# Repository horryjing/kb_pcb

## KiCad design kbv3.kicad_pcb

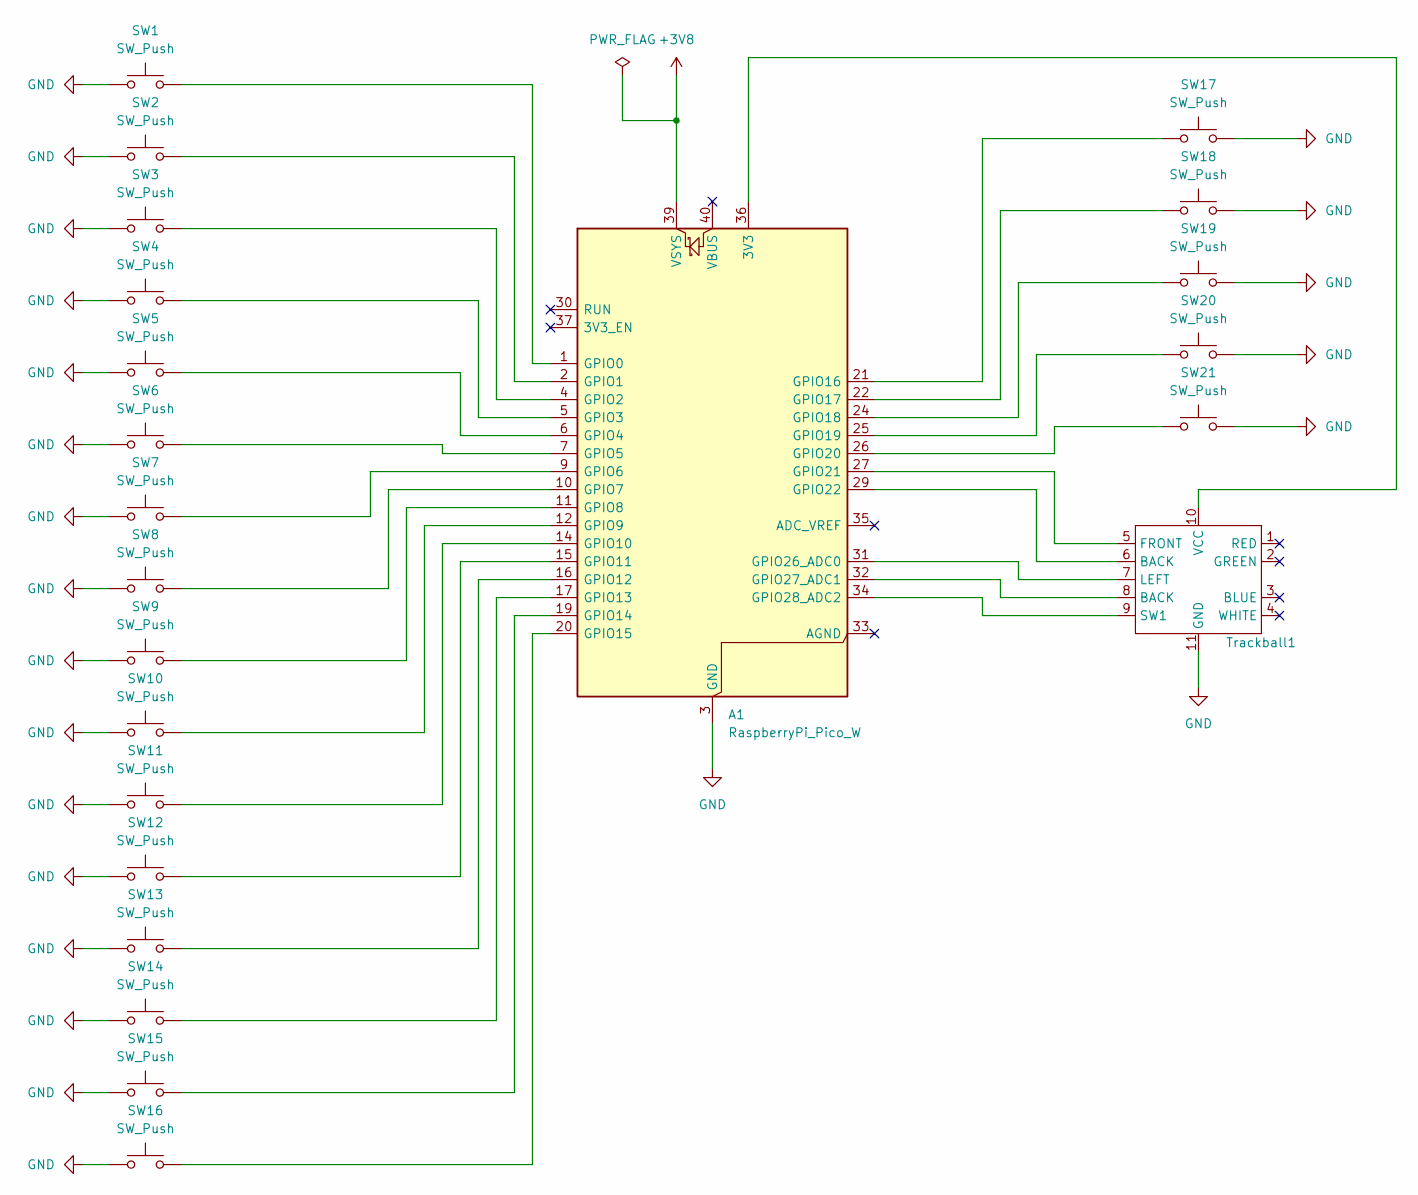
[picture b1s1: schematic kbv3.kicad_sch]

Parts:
A1: RaspberryPi_Pico_W; RaspberryPi_Pico_Common_THT
SW1, SW2, SW3, SW4, SW5, SW6, SW7, SW8, SW9, SW10, SW11, SW12, SW13, SW14, SW15, SW16, SW17, SW18, SW19, SW20, SW21: SW_Push; Kailh_socket_MX
Trackball1: Trackball_footprint

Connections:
+3V8: A1.39 (VSYS)
GND: A1.3 (GND), A1.8 (GND), A1.13 (GND), A1.18 (GND), A1.23 (GND), A1.28 (GND), A1.38 (GND), SW1.1, SW2.1, SW3.1, SW4.1, SW5.1, SW6.1, SW7.1, SW8.1, SW9.1, SW10.1, SW11.1, SW12.1, SW13.1, SW14.1, SW15.1, SW16.1, SW17.2, SW18.2, SW19.2, SW20.2, SW21.2, Trackball1.11 (GND)
unnamed: A1.1 (GPIO0), SW1.2
unnamed: A1.2 (GPIO1), SW2.2
unnamed: A1.4 (GPIO2), SW3.2
unnamed: A1.5 (GPIO3), SW4.2
unnamed: A1.6 (GPIO4), SW5.2
unnamed: A1.7 (GPIO5), SW6.2
unnamed: A1.9 (GPIO6), SW7.2
unnamed: A1.10 (GPIO7), SW8.2
unnamed: A1.11 (GPIO8), SW9.2
unnamed: A1.12 (GPIO9), SW10.2
unnamed: A1.14 (GPIO10), SW11.2
unnamed: A1.15 (GPIO11), SW12.2
unnamed: A1.16 (GPIO12), SW13.2
unnamed: A1.17 (GPIO13), SW14.2
unnamed: A1.19 (GPIO14), SW15.2
unnamed: A1.20 (GPIO15), SW16.2
unnamed: A1.21 (GPIO16), SW17.1
unnamed: A1.22 (GPIO17), SW18.1
unnamed: A1.24 (GPIO18), SW19.1
unnamed: A1.25 (GPIO19), SW20.1
unnamed: A1.26 (GPIO20), SW21.1
unnamed: A1.27 (GPIO21), Trackball1.5 (FRONT)
unnamed: A1.29 (GPIO22), Trackball1.6 (BACK)
unnamed: A1.31 (GPIO26_ADC0), Trackball1.7 (LEFT)
unnamed: A1.32 (GPIO27_ADC1), Trackball1.8 (BACK)
unnamed: A1.34 (GPIO28_ADC2), Trackball1.9 (SW1)
unnamed: A1.36 (3V3), Trackball1.10 (VCC)

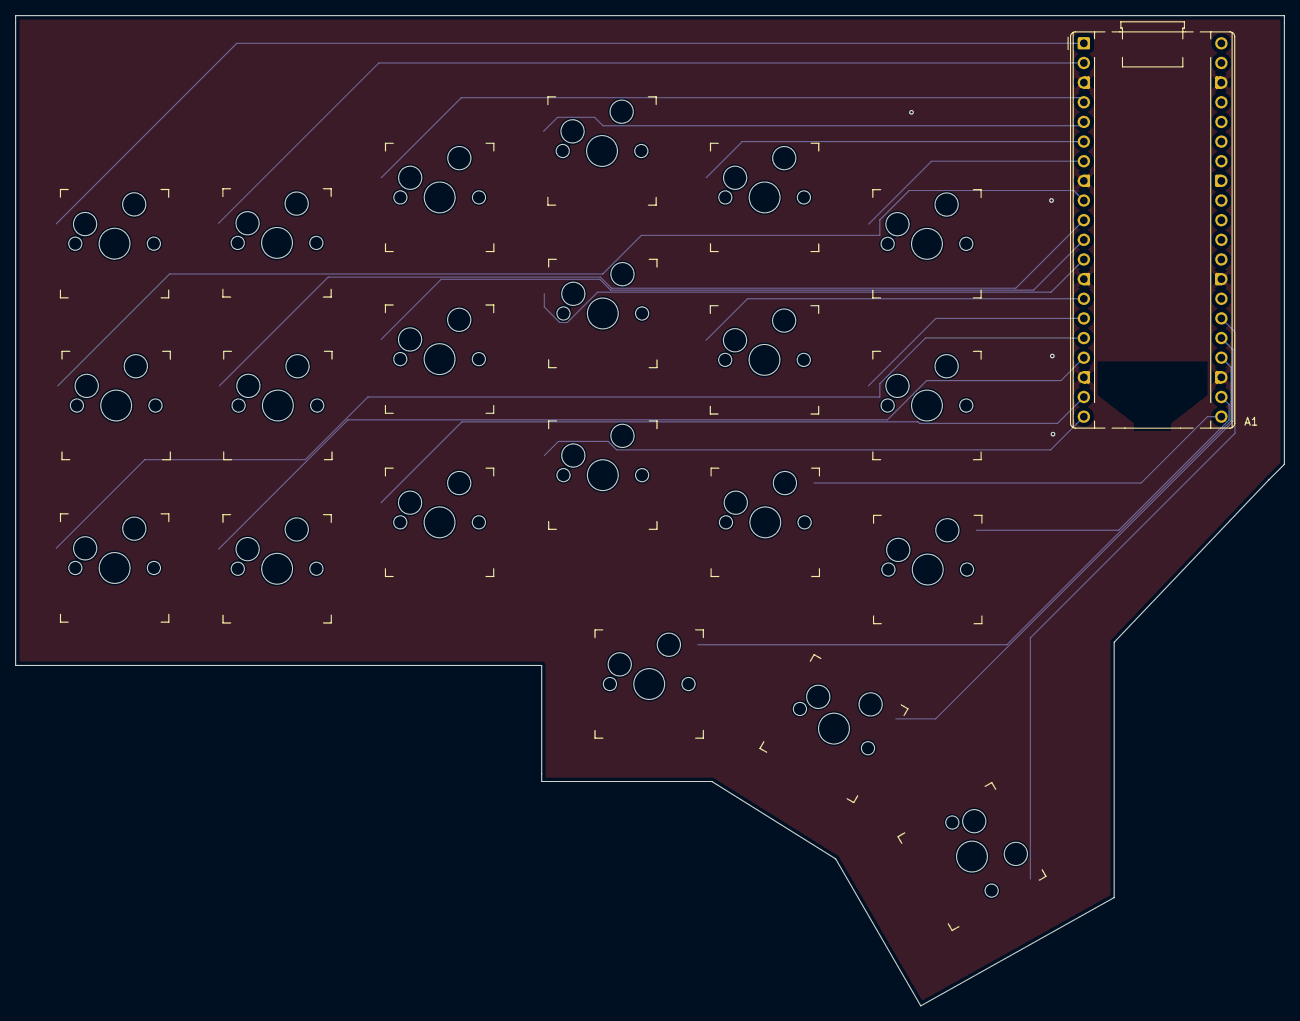
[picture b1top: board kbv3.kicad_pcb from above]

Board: 4 copper layers, 164.0 x 128.0 mm, 22 parts (0 on the bottom side), 22 nets.

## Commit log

2025-09-28 left and right
2025-09-28 jlcpcb validated
2025-09-28 jclpcb templates
2025-10-29 reviewed version
2025-10-29 generate berber file
2025-10-29 change 4 layers to 2 layers
2025-11-01 gerber
2025-12-21 pcb kb case bottom left and right
2025-12-23 improve pcb bottom case support width and hight
